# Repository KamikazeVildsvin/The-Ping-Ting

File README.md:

# The Ping Ting
This repository contains the KiCad files and the design files for *The Ping Ting*.

The Ping Ting is a single PCB with three different high-Q state variable filters, which are intended to be used for "filter pinging".
The board can be supplied from a typical 9V-12V DC center positive power supply.

## Images

### 3D Model

### PCB

### Schematic

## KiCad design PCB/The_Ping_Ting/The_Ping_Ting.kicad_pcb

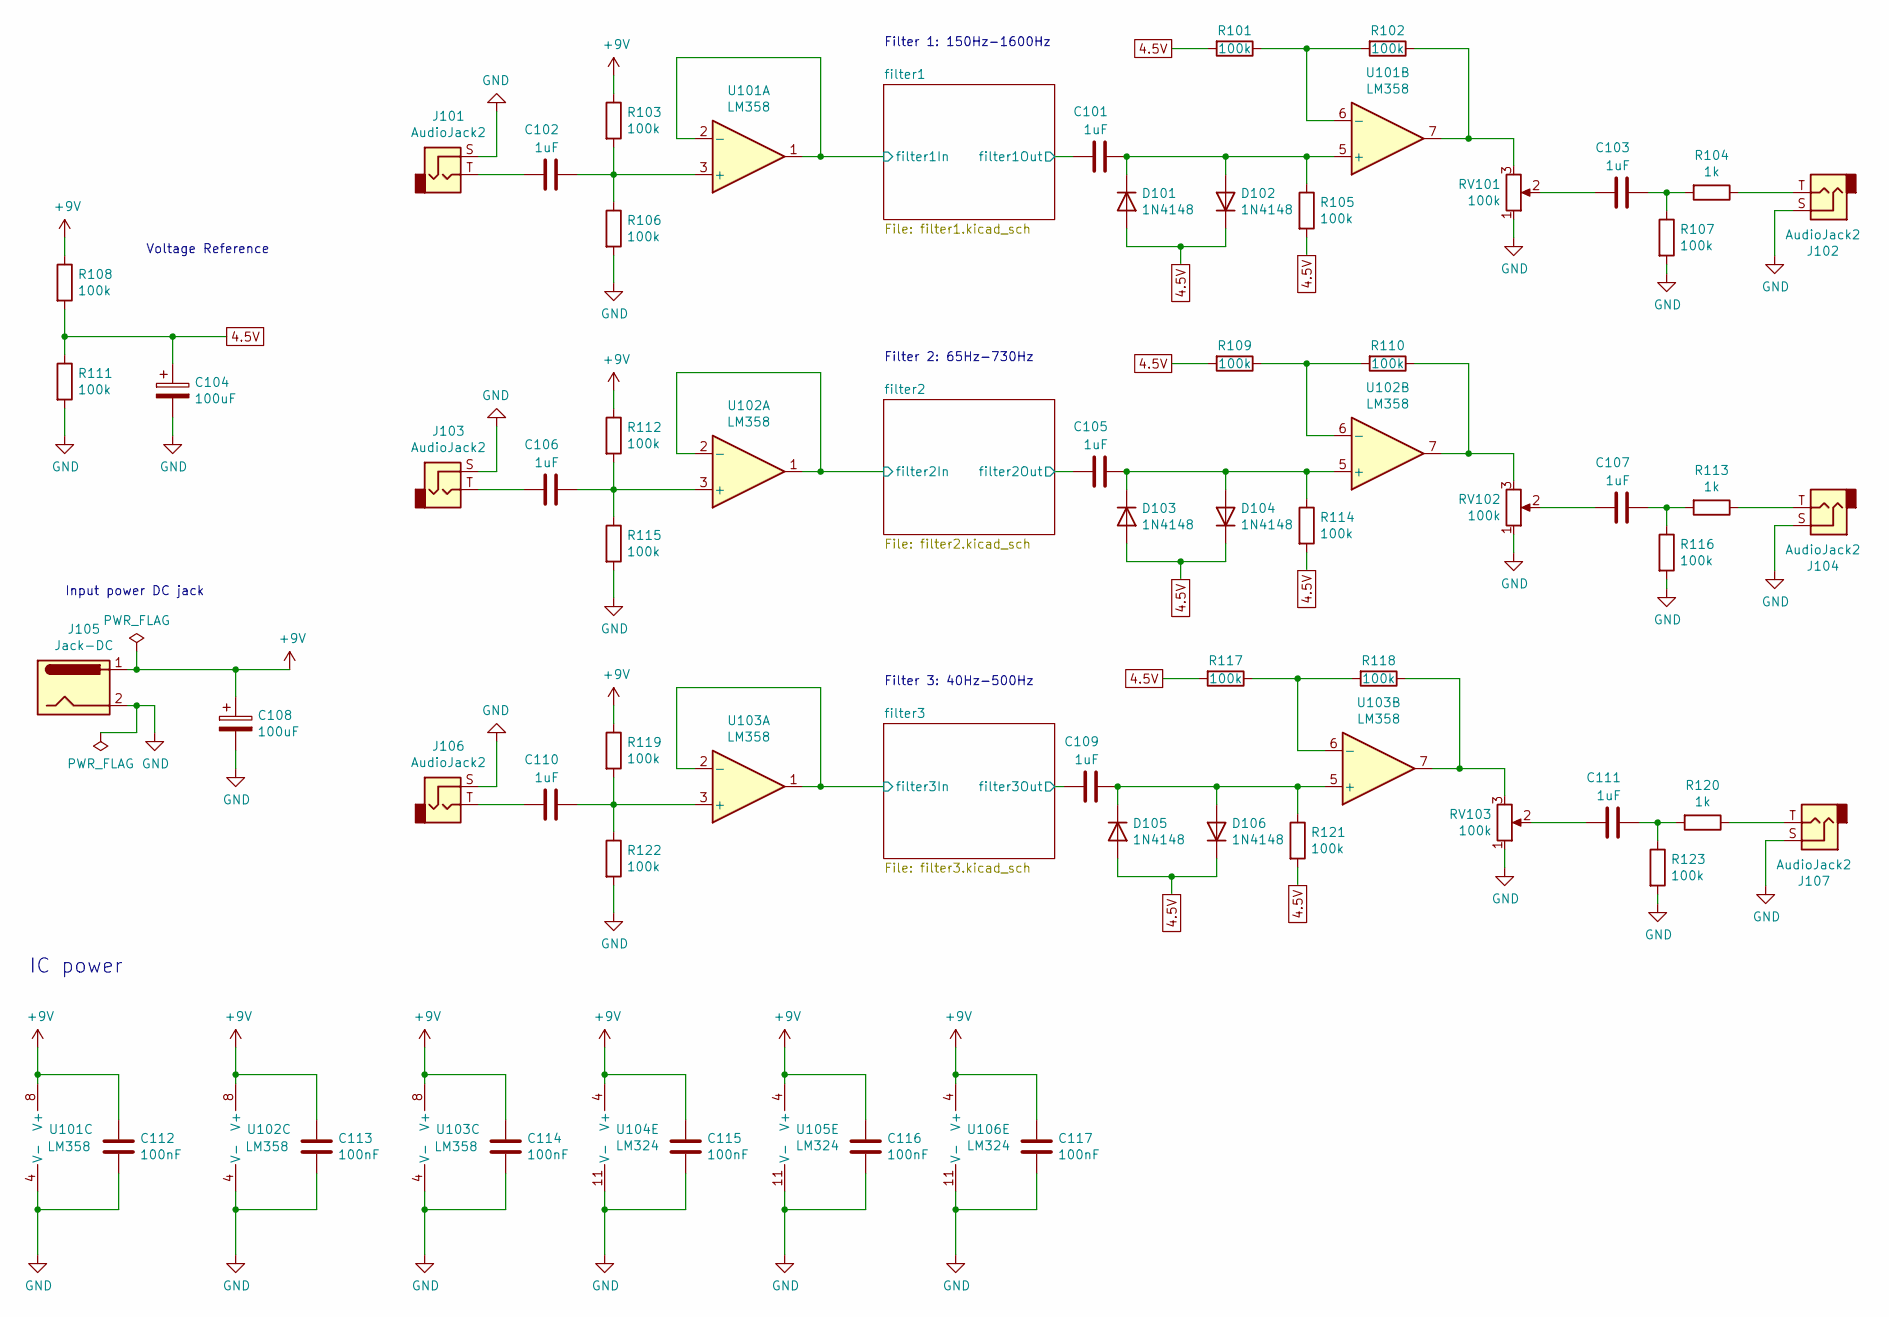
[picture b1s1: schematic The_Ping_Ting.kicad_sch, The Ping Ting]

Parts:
C101, C102, C103, C105, C106, C107, C109, C110, C111: 1uF; C_Axial_L22.0mm_D10.5mm_P27.50mm_Horizontal
C104, C108: 100uF; CP_Radial_D6.3mm_P2.50mm
C112, C113, C114, C115, C116, C117: 100nF; C_Disc_D5.0mm_W2.5mm_P5.00mm
D101, D102, D103, D104, D105, D106: 1N4148; D_DO-35_SOD27_P7.62mm_Horizontal
J101, J102, J103, J104, J106, J107: AudioJack2; Jack_6.35mm_Neutrik_NJ2FD-V_Vertical
J105: Jack-DC; Molex_KK-254_AE-6410-02A_1x02_P2.54mm_Vertical
R101, R102, R103, R105, R106, R107, R108, R109, R110, R111, R112, R114, R115, R116, R117, R118, R119, R121, R122, R123: 100k; R_Axial_DIN0207_L6.3mm_D2.5mm_P10.16mm_Horizontal
R104, R113, R120: 1k; R_Axial_DIN0207_L6.3mm_D2.5mm_P10.16mm_Horizontal
RV101, RV102, RV103: 100k; PinHeader_1x03_P2.54mm_Vertical
U101, U102, U103: LM358; DIP-8_W7.62mm
U104, U105, U106: LM324; DIP-14_W7.62mm

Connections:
4.5V: C104.1, D101.2 (A), D102.1 (K), D103.2 (A), D104.1 (K), D105.2 (A), D106.1 (K), R101.2, R105.2, R108.2, R109.2, R111.1, R114.2, R117.2, R121.2; also elsewhere on the board
+9V: C108.1, C112.1, C113.1, C114.1, C115.1, C116.1, C117.1, J105.1, R103.1, R108.1, R112.1, R119.1, U101.8 (V+), U102.8 (V+), U103.8 (V+), U104.4 (V+), U105.4 (V+), U106.4 (V+)
/filter1/filter1In: U101.1, U101.2 (-); also elsewhere on the board
/filter1/filter1Out: C101.1; also elsewhere on the board
/filter2/filter2In: U102.1, U102.2 (-); also elsewhere on the board
/filter2/filter2Out: C105.1; also elsewhere on the board
/filter3/filter3In: U103.1, U103.2 (-); also elsewhere on the board
/filter3/filter3Out: C109.1; also elsewhere on the board
GND: C104.2, C108.2, C112.2, C113.2, C114.2, C115.2, C116.2, C117.2, J101.S, J102.S, J103.S, J104.S, J105.2, J106.S, J107.S, R106.2, R107.2, R111.2, R115.2, R116.2, R122.2, R123.2, RV101.1, RV102.1, RV103.1, U101.4 (V-), U102.4 (V-), U103.4 (V-), U104.11 (V-), U105.11 (V-), U106.11 (V-)
unnamed: C102.1, J101.T
unnamed: C103.1, RV101.2
unnamed: C103.2, R104.2, R107.1
unnamed: C106.1, J103.T
unnamed: C107.1, RV102.2
unnamed: C107.2, R113.2, R116.1
unnamed: C110.1, J106.T
unnamed: C111.1, RV103.2
unnamed: C111.2, R120.2, R123.1
unnamed: C101.2, D101.1 (K), D102.2 (A), R105.1, U101.5 (+)
unnamed: C105.2, D103.1 (K), D104.2 (A), R114.1, U102.5 (+)
unnamed: C109.2, D105.1 (K), D106.2 (A), R121.1, U103.5 (+)
unnamed: J102.T, R104.1
unnamed: J104.T, R113.1
unnamed: J107.T, R120.1
unnamed: R102.1, RV101.3, U101.7
unnamed: R110.1, RV102.3, U102.7
unnamed: R118.1, RV103.3, U103.7
unnamed: C102.2, R103.2, R106.1, U101.3 (+)
unnamed: R101.1, R102.2, U101.6 (-)
unnamed: C106.2, R112.2, R115.1, U102.3 (+)
unnamed: R109.1, R110.2, U102.6 (-)
unnamed: C110.2, R119.2, R122.1, U103.3 (+)
unnamed: R117.1, R118.2, U103.6 (-)

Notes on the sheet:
Filter 1: 150Hz-1600Hz
IC power
Input power DC jack
Filter 3: 40Hz-500Hz
Filter 2: 65Hz-730Hz
Voltage Reference

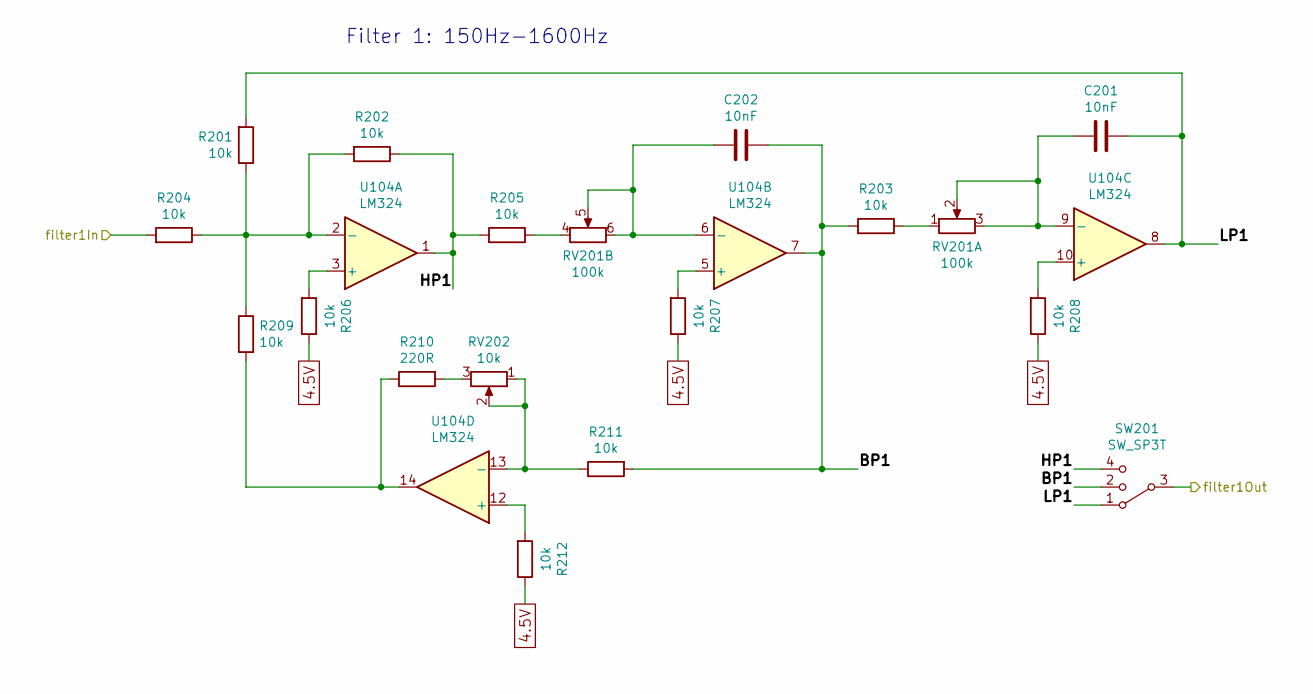
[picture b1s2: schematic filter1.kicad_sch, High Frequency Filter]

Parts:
C201, C202: 10nF; C_Rect_L7.2mm_W5.5mm_P5.00mm_FKS2_FKP2_MKS2_MKP2
R201, R202, R203, R204, R205, R206, R207, R208, R209, R211, R212: 10k; R_Axial_DIN0207_L6.3mm_D2.5mm_P10.16mm_Horizontal
R210: 220R; R_Axial_DIN0207_L6.3mm_D2.5mm_P10.16mm_Horizontal
RV201: 100k; PinHeader_1x06_P2.54mm_Vertical
RV202: 10k; PinHeader_1x03_P2.54mm_Vertical
SW201: SW_SP3T; PinHeader_1x04_P2.54mm_Vertical
U104: LM324; DIP-14_W7.62mm

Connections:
4.5V: R206.1, R207.1, R208.1, R212.1; also elsewhere on the board
/filter1/BP1: C202.1, R203.2, R211.2, SW201.2, U104.7
/filter1/HP1: R202.1, R205.2, SW201.4, U104.1
/filter1/LP1: C201.1, R201.2, SW201.1, U104.8
/filter1/filter1In: R204.2; also elsewhere on the board
/filter1/filter1Out: SW201.3; also elsewhere on the board
unnamed: R203.1, RV201.1
unnamed: R205.1, RV201.4
unnamed: R209.2, R210.1, U104.14
unnamed: R210.2, RV202.3
unnamed: R206.2, U104.3 (+)
unnamed: R201.1, R202.2, R204.1, R209.1, U104.2 (-)
unnamed: R207.2, U104.5 (+)
unnamed: C202.2, RV201.5, RV201.6, U104.6 (-)
unnamed: R208.2, U104.10 (+)
unnamed: C201.2, RV201.2, RV201.3, U104.9 (-)
unnamed: R212.2, U104.12 (+)
unnamed: R211.1, RV202.1, RV202.2, U104.13 (-)

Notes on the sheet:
Filter 1: 150Hz-1600Hz

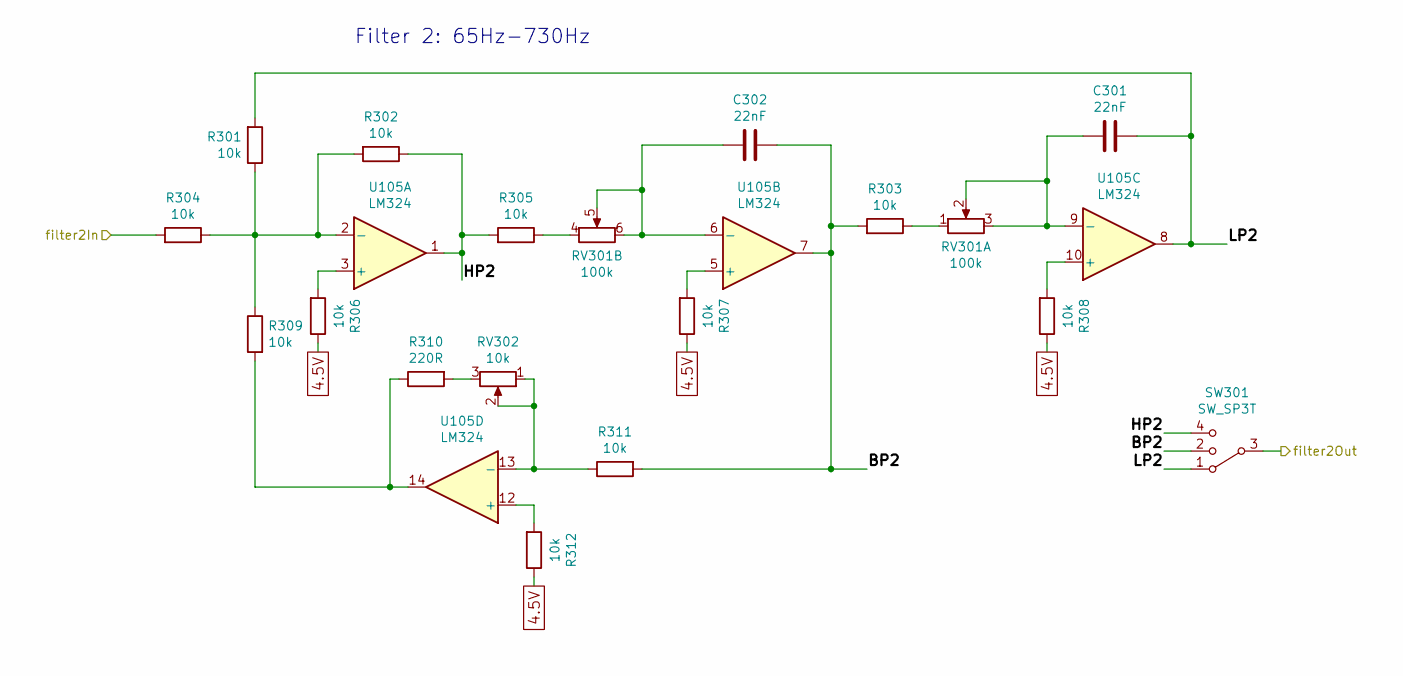
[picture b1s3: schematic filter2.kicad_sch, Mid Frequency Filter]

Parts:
C301, C302: 22nF; C_Rect_L7.2mm_W7.2mm_P5.00mm_FKS2_FKP2_MKS2_MKP2
R301, R302, R303, R304, R305, R306, R307, R308, R309, R311, R312: 10k; R_Axial_DIN0207_L6.3mm_D2.5mm_P10.16mm_Horizontal
R310: 220R; R_Axial_DIN0207_L6.3mm_D2.5mm_P10.16mm_Horizontal
RV301: 100k; PinHeader_1x06_P2.54mm_Vertical
RV302: 10k; PinHeader_1x03_P2.54mm_Vertical
SW301: SW_SP3T; PinHeader_1x04_P2.54mm_Vertical
U105: LM324; DIP-14_W7.62mm

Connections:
4.5V: R306.1, R307.1, R308.1, R312.1; also elsewhere on the board
/filter2/BP2: C302.1, R303.2, R311.2, SW301.2, U105.7
/filter2/HP2: R302.1, R305.2, SW301.4, U105.1
/filter2/LP2: C301.1, R301.2, SW301.1, U105.8
/filter2/filter2In: R304.2; also elsewhere on the board
/filter2/filter2Out: SW301.3; also elsewhere on the board
unnamed: R303.1, RV301.1
unnamed: R305.1, RV301.4
unnamed: R309.2, R310.1, U105.14
unnamed: R310.2, RV302.3
unnamed: R306.2, U105.3 (+)
unnamed: R301.1, R302.2, R304.1, R309.1, U105.2 (-)
unnamed: R307.2, U105.5 (+)
unnamed: C302.2, RV301.5, RV301.6, U105.6 (-)
unnamed: R308.2, U105.10 (+)
unnamed: C301.2, RV301.2, RV301.3, U105.9 (-)
unnamed: R312.2, U105.12 (+)
unnamed: R311.1, RV302.1, RV302.2, U105.13 (-)

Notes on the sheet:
Filter 2: 65Hz-730Hz

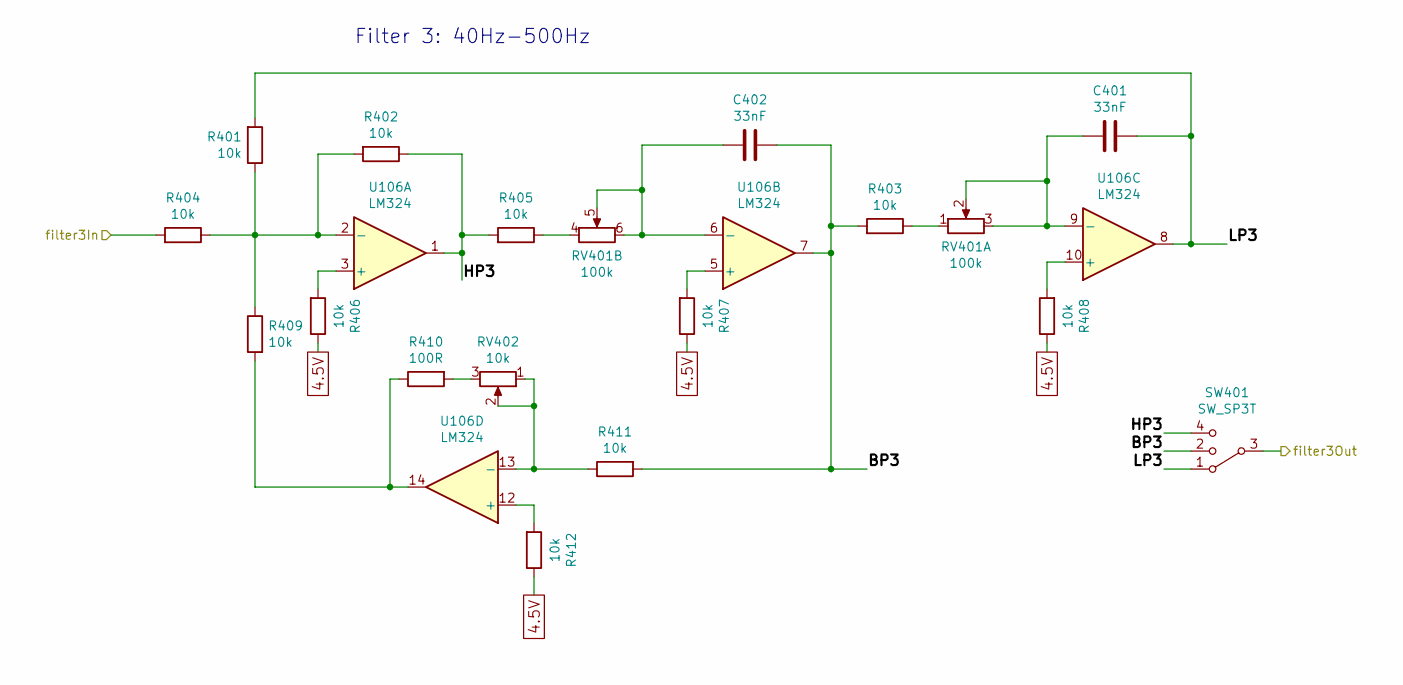
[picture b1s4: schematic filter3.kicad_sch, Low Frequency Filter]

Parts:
C401, C402: 33nF; C_Rect_L7.2mm_W8.5mm_P5.00mm_FKP2_FKP2_MKS2_MKP2
R401, R402, R403, R404, R405, R406, R407, R408, R409, R411, R412: 10k; R_Axial_DIN0207_L6.3mm_D2.5mm_P10.16mm_Horizontal
R410: 100R; R_Axial_DIN0207_L6.3mm_D2.5mm_P10.16mm_Horizontal
RV401: 100k; PinHeader_1x06_P2.54mm_Vertical
RV402: 10k; PinHeader_1x03_P2.54mm_Vertical
SW401: SW_SP3T; PinHeader_1x04_P2.54mm_Vertical
U106: LM324; DIP-14_W7.62mm

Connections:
4.5V: R406.1, R407.1, R408.1, R412.1; also elsewhere on the board
/filter3/BP3: C402.1, R403.2, R411.2, SW401.2, U106.7
/filter3/HP3: R402.1, R405.2, SW401.4, U106.1
/filter3/LP3: C401.1, R401.2, SW401.1, U106.8
/filter3/filter3In: R404.2; also elsewhere on the board
/filter3/filter3Out: SW401.3; also elsewhere on the board
unnamed: R403.1, RV401.1
unnamed: R405.1, RV401.4
unnamed: R409.2, R410.1, U106.14
unnamed: R410.2, RV402.3
unnamed: R406.2, U106.3 (+)
unnamed: R401.1, R402.2, R404.1, R409.1, U106.2 (-)
unnamed: R407.2, U106.5 (+)
unnamed: C402.2, RV401.5, RV401.6, U106.6 (-)
unnamed: R408.2, U106.10 (+)
unnamed: C401.2, RV401.2, RV401.3, U106.9 (-)
unnamed: R412.2, U106.12 (+)
unnamed: R411.1, RV402.1, RV402.2, U106.13 (-)

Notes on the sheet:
Filter 3: 40Hz-500Hz

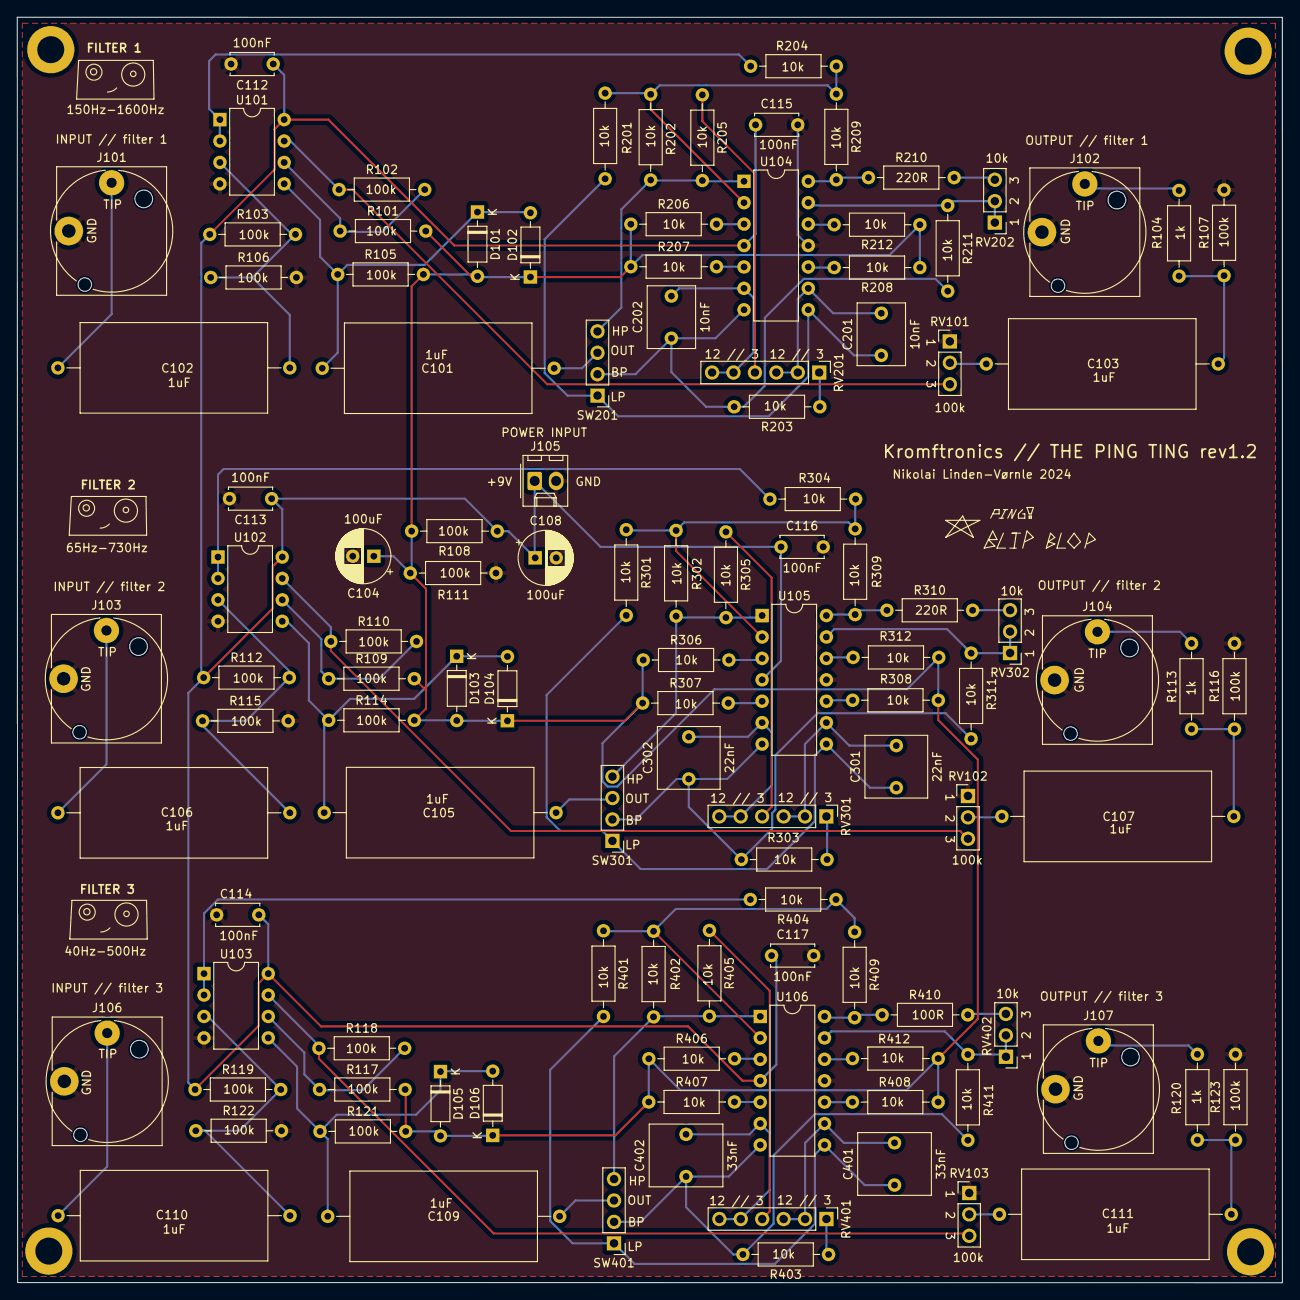
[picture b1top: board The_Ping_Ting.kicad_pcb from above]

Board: 2 copper layers, 150.0 x 150.1 mm, 113 parts (0 on the bottom side), 78 nets.

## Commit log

2024-06-11 initial commit.
2024-06-11 Create LICENSE
2024-06-11 added images of PCB, 3D model and schematic.
2024-09-07 REVV 1.2 - Updated resonance feedback resistance Updated the feedback resistance in the mid and high frequency feedback circuit to get a more "stable" resonance level.
